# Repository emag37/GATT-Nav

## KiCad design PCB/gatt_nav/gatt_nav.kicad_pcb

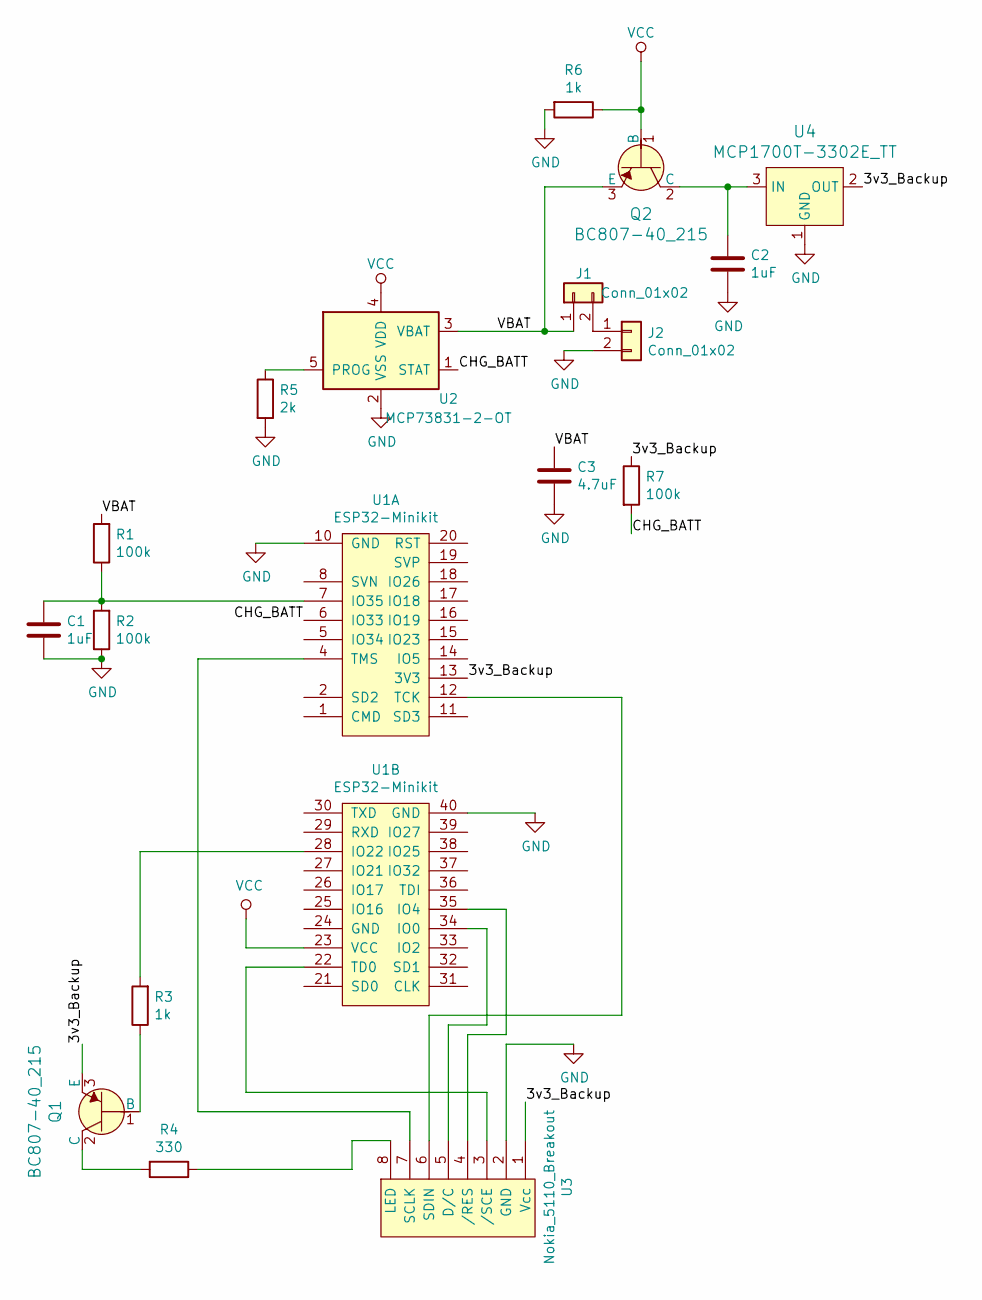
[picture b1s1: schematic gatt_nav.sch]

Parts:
C1, C2: 1uF; C_0805_HandSoldering; Digi-Key_PN 1276-1066-1-ND
C3: 4.7uF; C_0805_HandSoldering; Digi-Key_PN 732-7623-1-ND
J1, J2: Conn_01x02; PINHEAD1-2
Q1, Q2: BC807-40_215; SOT-23-3; MPN BC807-40,215; Digi-Key_PN 1727-2917-1-ND
R1, R2, R7: 100k; R_0805_HandSoldering; Digi-Key_PN RMCF0805FT100KCT-ND
R3, R6: 1k; R_0805_HandSoldering; Digi-Key_PN RNCP0805FTD1K00CT-ND
R4: 330; R_0805_HandSoldering; Digi-Key_PN A129743CT-ND
R5: 2k; R_0805_HandSoldering
U1: ESP32-Minikit
U2: MCP73831-2-OT; SOT-23-5_HandSoldering
U3: Nokia_5110_Breakout
U4: MCP1700T-3302E_TT; SOT-23-3; MPN MCP1700T-3302E/TT; Digi-Key_PN MCP1700T3302ETTCT-ND

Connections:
/3v3_Backup: Q1.3 (E), R7.1, U1.13 (3V3), U3.1 (Vcc), U4.2 (OUT)
/CHG_BATT: R7.2, U1.6 (IO33), U2.1 (STAT)
/VBAT: C3.1, J1.1, Q2.3 (E), R1.2, U2.3 (VBAT)
GND: C1.2, C2.2, C3.2, J2.2, R2.1, R5.2, R6.2, U1.10 (GND), U1.40 (GND), U2.2 (VSS), U3.2 (GND), U4.1 (GND)
unnamed: C1.1, R1.1, R2.2, U1.7 (IO35)
unnamed: C2.1, Q2.2 (C), U4.3 (IN)
unnamed: J1.2, J2.1
unnamed: Q1.1 (B), R3.1
unnamed: Q1.2 (C), R4.2
unnamed: R3.2, U1.28 (IO22)
unnamed: R4.1, U3.8 (LED)
unnamed: R5.1, U2.5 (PROG)
unnamed: U1.4 (TMS), U3.7 (SCLK)
unnamed: U1.12 (TCK), U3.6 (SDIN)
unnamed: U1.22 (TD0), U3.3 (/SCE)
unnamed: U1.34 (IO0), U3.5 (D/C)
unnamed: U1.35 (IO4), U3.4 (/RES)
VCC: Q2.1 (B), R6.1, U1.23 (VCC), U2.4 (VDD)

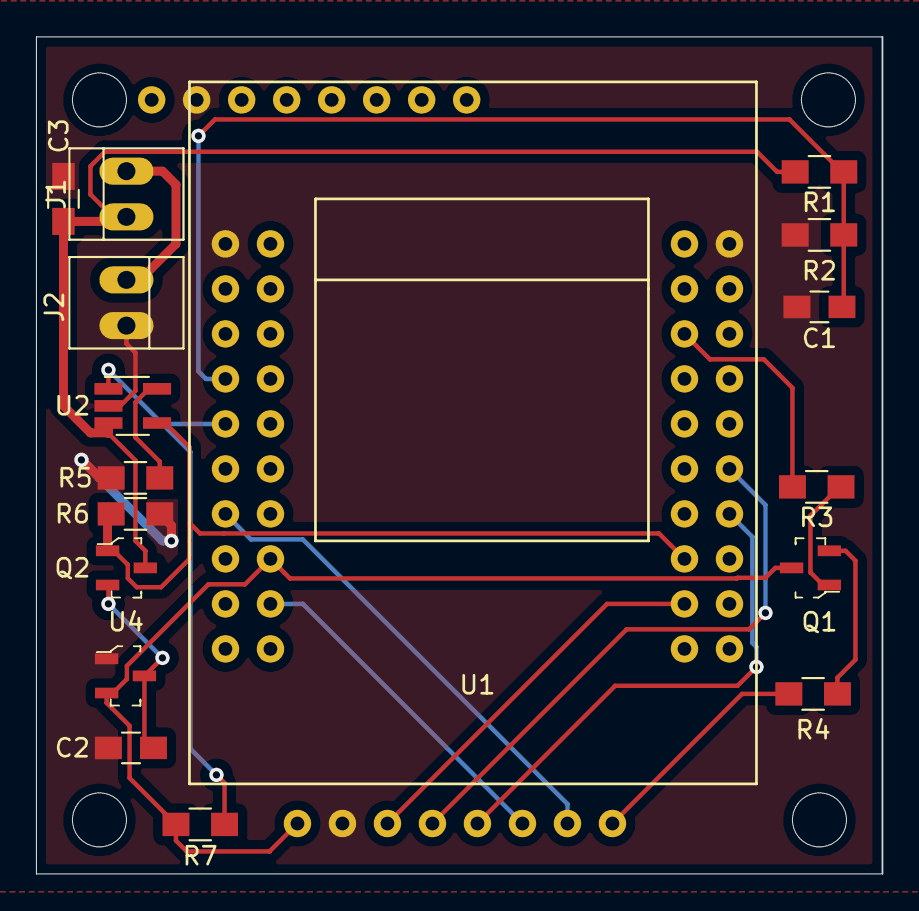
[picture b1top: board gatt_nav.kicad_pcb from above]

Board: 2 copper layers, 47.0 x 46.5 mm, 18 parts (1 on the bottom side), 18 nets.

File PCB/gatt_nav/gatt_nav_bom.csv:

Collated Components:,,,,,,,,,,,,,,,
,,,,,,,,,,,,,,,
Item,Qty,Reference(s),Value,LibPart,Footprint,Datasheet,Category,DK_Datasheet_Link,DK_Detail_Page,Description,Digi-Key_PN,Family,MPN,Manufacturer,Status
1,2,"C1, C2",1uF,Device:C,Capacitors_SMD:C_0805_HandSoldering,~,,,,,1276-1066-1-ND,,,,
2,1,C3,4.7uF,Device:C,Capacitors_SMD:C_0805_HandSoldering,~,,,,,732-7623-1-ND,,,,
3,2,"J1, J2",Conn_01x02,Connector_Generic:Conn_01x02,Connectors:PINHEAD1-2,~,,,,,,,,,
4,2,"Q1, Q2",BC807-40_215,dk_Transistors-Bipolar-BJT-Single:BC807-40_215,digikey-footprints:SOT-23-3,https://assets.nexperia.com/documents/data-sheet/BC807_BC807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,Discrete Semiconductor Products,https://assets.nexperia.com/documents/data-sheet/BC807_BC807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,"/product-detail/en/nexperia-usa-inc/BC807-40,215/1727-2917-1-ND/763456",TRANS PNP 45V 0.5A SOT23,1727-2917-1-ND,Transistors - Bipolar (BJT) - Single,"BC807-40,215",Nexperia USA Inc.,Active
5,3,"R1, R2, R7",100k,Device:R,Resistors_SMD:R_0805_HandSoldering,~,,,,,RMCF0805FT100KCT-ND,,,,
6,2,"R3, R6",1k,Device:R,Resistors_SMD:R_0805_HandSoldering,~,,,,,RNCP0805FTD1K00CT-ND,,,,
7,1,R4,330,Device:R,Resistors_SMD:R_0805_HandSoldering,~,,,,,A129743CT-ND,,,,
8,1,R5,2k,Device:R,Resistors_SMD:R_0805_HandSoldering,~,,,,,,,,,
9,1,U1,ESP32-Minikit,eric_parts:ESP32-Minikit,dev:ESP32-Minikit,,,,,,,,,,
10,1,U2,MCP73831-2-OT,Battery_Management:MCP73831-2-OT,TO_SOT_Packages_SMD:SOT-23-5_HandSoldering,http://ww1.microchip.com/downloads/en/DeviceDoc/20001984g.pdf,,,,,,,,,
11,1,U3,Nokia_5110_Breakout,eric_parts:Nokia_5110_Breakout,dev:Nokia_5110_Breakout,,,,,,,,,,
12,1,U4,MCP1700T-3302E_TT,dk_PMIC-Voltage-Regulators-Linear:MCP1700T-3302E_TT,digikey-footprints:SOT-23-3,http://www.microchip.com/mymicrochip/filehandler.aspx?ddocna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,Integrated Circuits (ICs),http://www.microchip.com/mymicrochip/filehandler.aspx?ddocna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,/product-detail/en/microchip-technology/MCP1700T-3302E-TT/MCP1700T3302ETTCT-ND/652677,IC REG LINEAR 3.3V 250MA SOT23-3,MCP1700T3302ETTCT-ND,PMIC - Voltage Regulators - Linear,MCP1700T-3302E/TT,Microchip Technology,Active

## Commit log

2019-06-14 Initial commit, WIP refactoring BLE to send array of floats
2019-06-14 BLE sends array of 3 floats with one characteristic, status callback
2019-06-29 Working lcd test!
2019-08-20 Working PCB
2020-09-29 Works with GPS bearing, use PlatformIO for Arduino
2020-10-05 Android will not report GPS if distance is too small, Arduino will not update screen if distance is invalid (negative)
2020-10-10 Remove PCB
2020-11-03 Android: Filter bearing to avoid spurious errors, cleanup code ESP32: Refactor code, reconnects correctly when server not online for a while
2020-11-03 Remove .gitmodules
2020-11-07 Remove unused display code Add script to generate image array Refactor nav screen layout
2020-12-15 Use a real PlatformIO project instead of an adapted Arduino project. Use custom sdkconfig
2021-02-20 Suspend bluetooth when sleeping and reconnect on wakeup. Power savings!
2021-02-28 Use ULP to reduce backlight power consumption, other fixes to avoid crashes when resetting BLE client. Serial logger uses ESP logging.
2021-02-28 Index blue column in Python image generator script:
2021-03-13 Seperate data from update function, modernize adc on/off methods
